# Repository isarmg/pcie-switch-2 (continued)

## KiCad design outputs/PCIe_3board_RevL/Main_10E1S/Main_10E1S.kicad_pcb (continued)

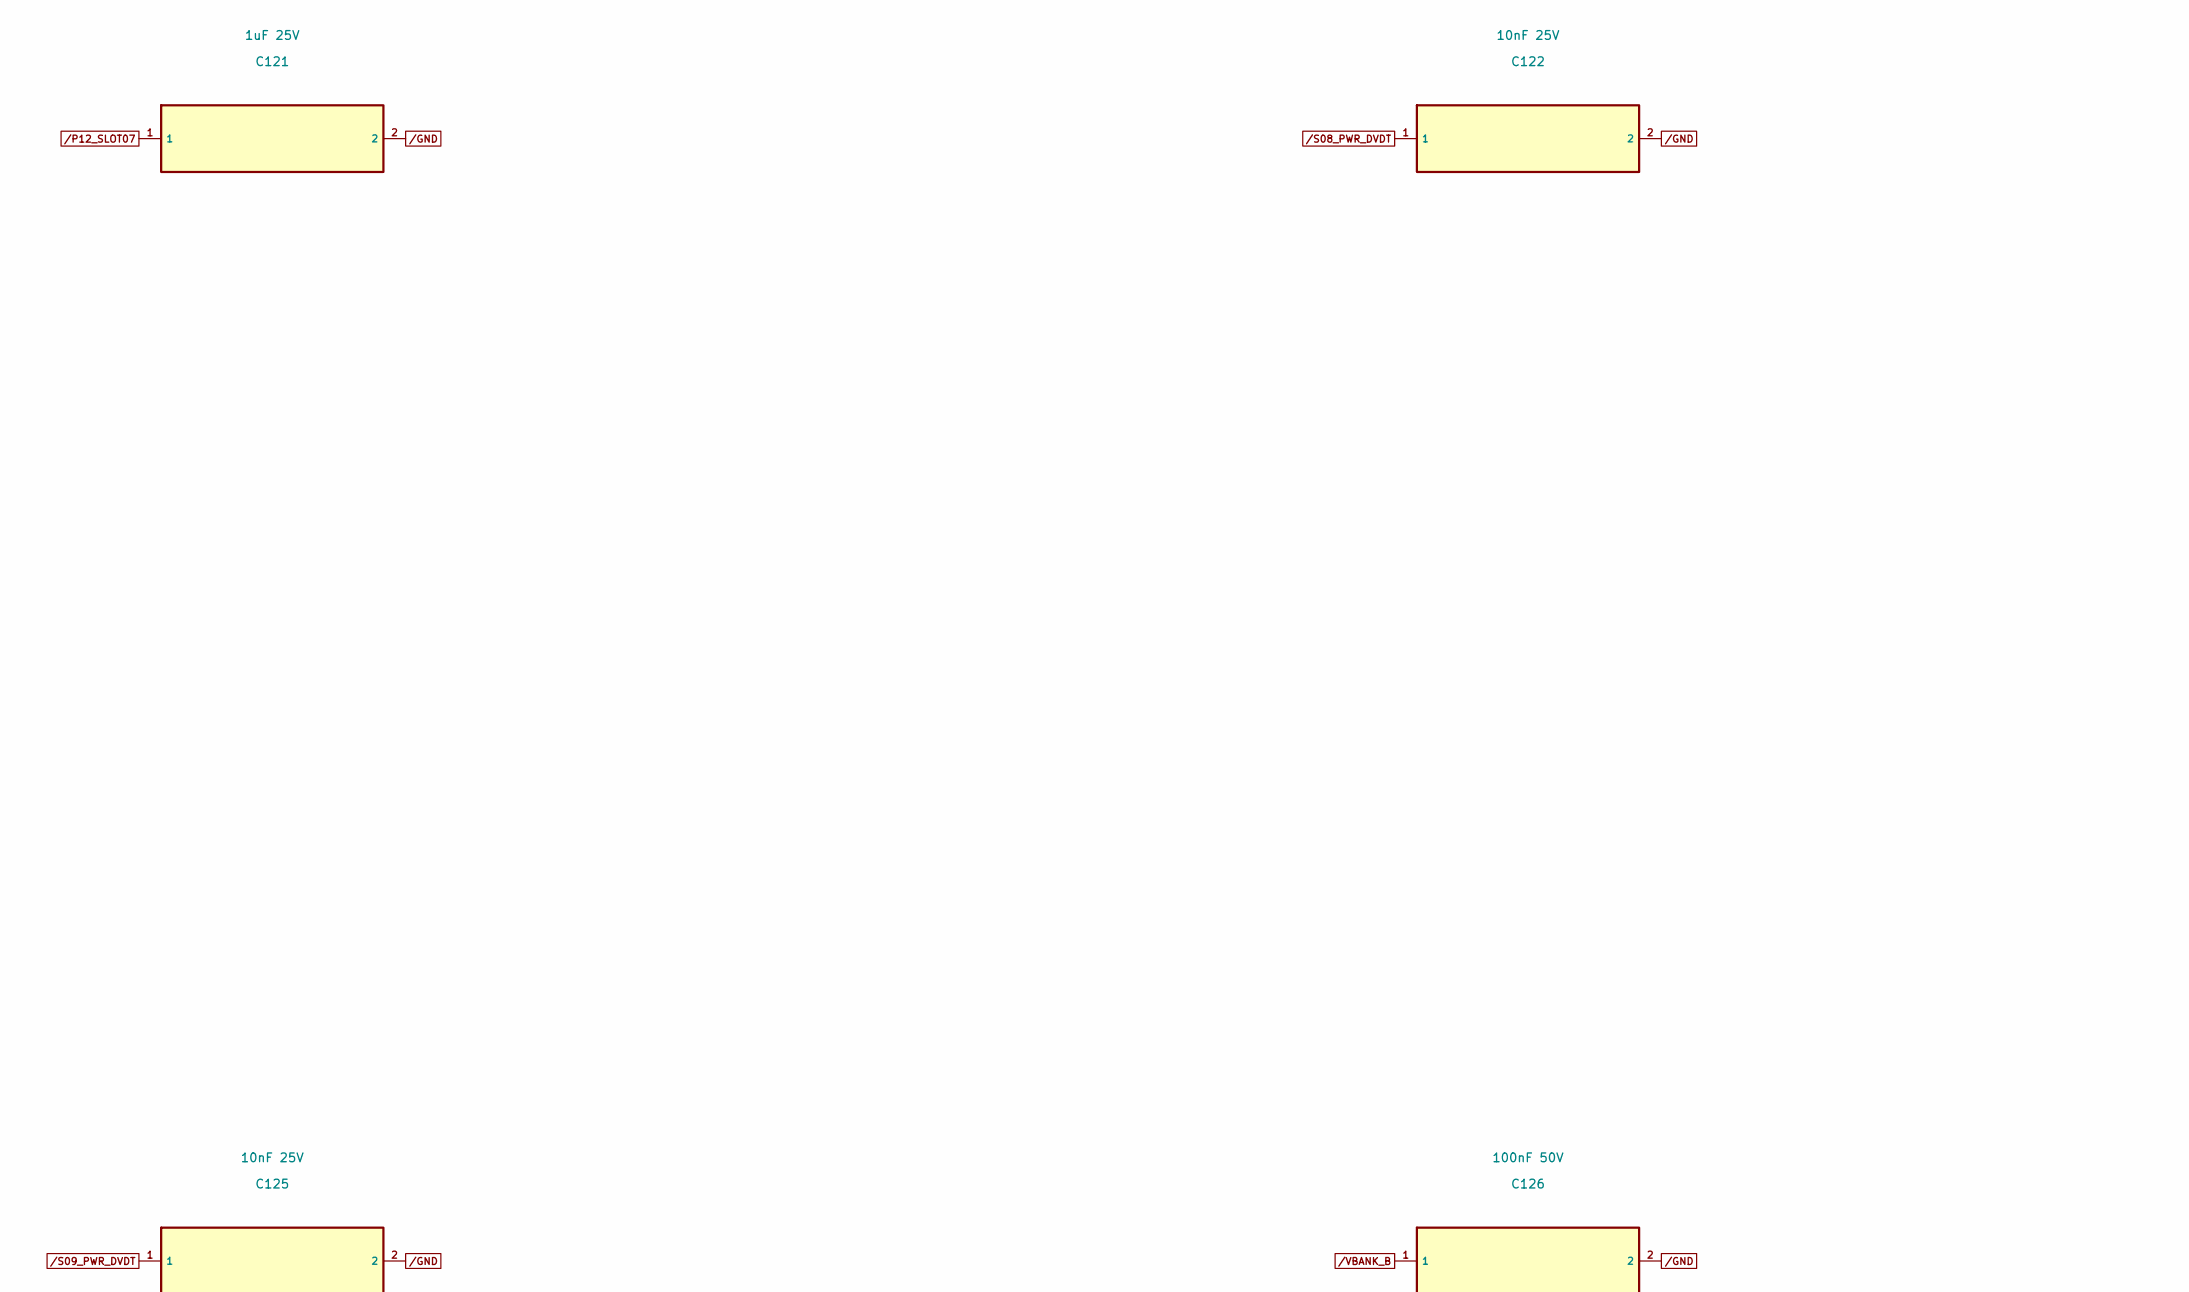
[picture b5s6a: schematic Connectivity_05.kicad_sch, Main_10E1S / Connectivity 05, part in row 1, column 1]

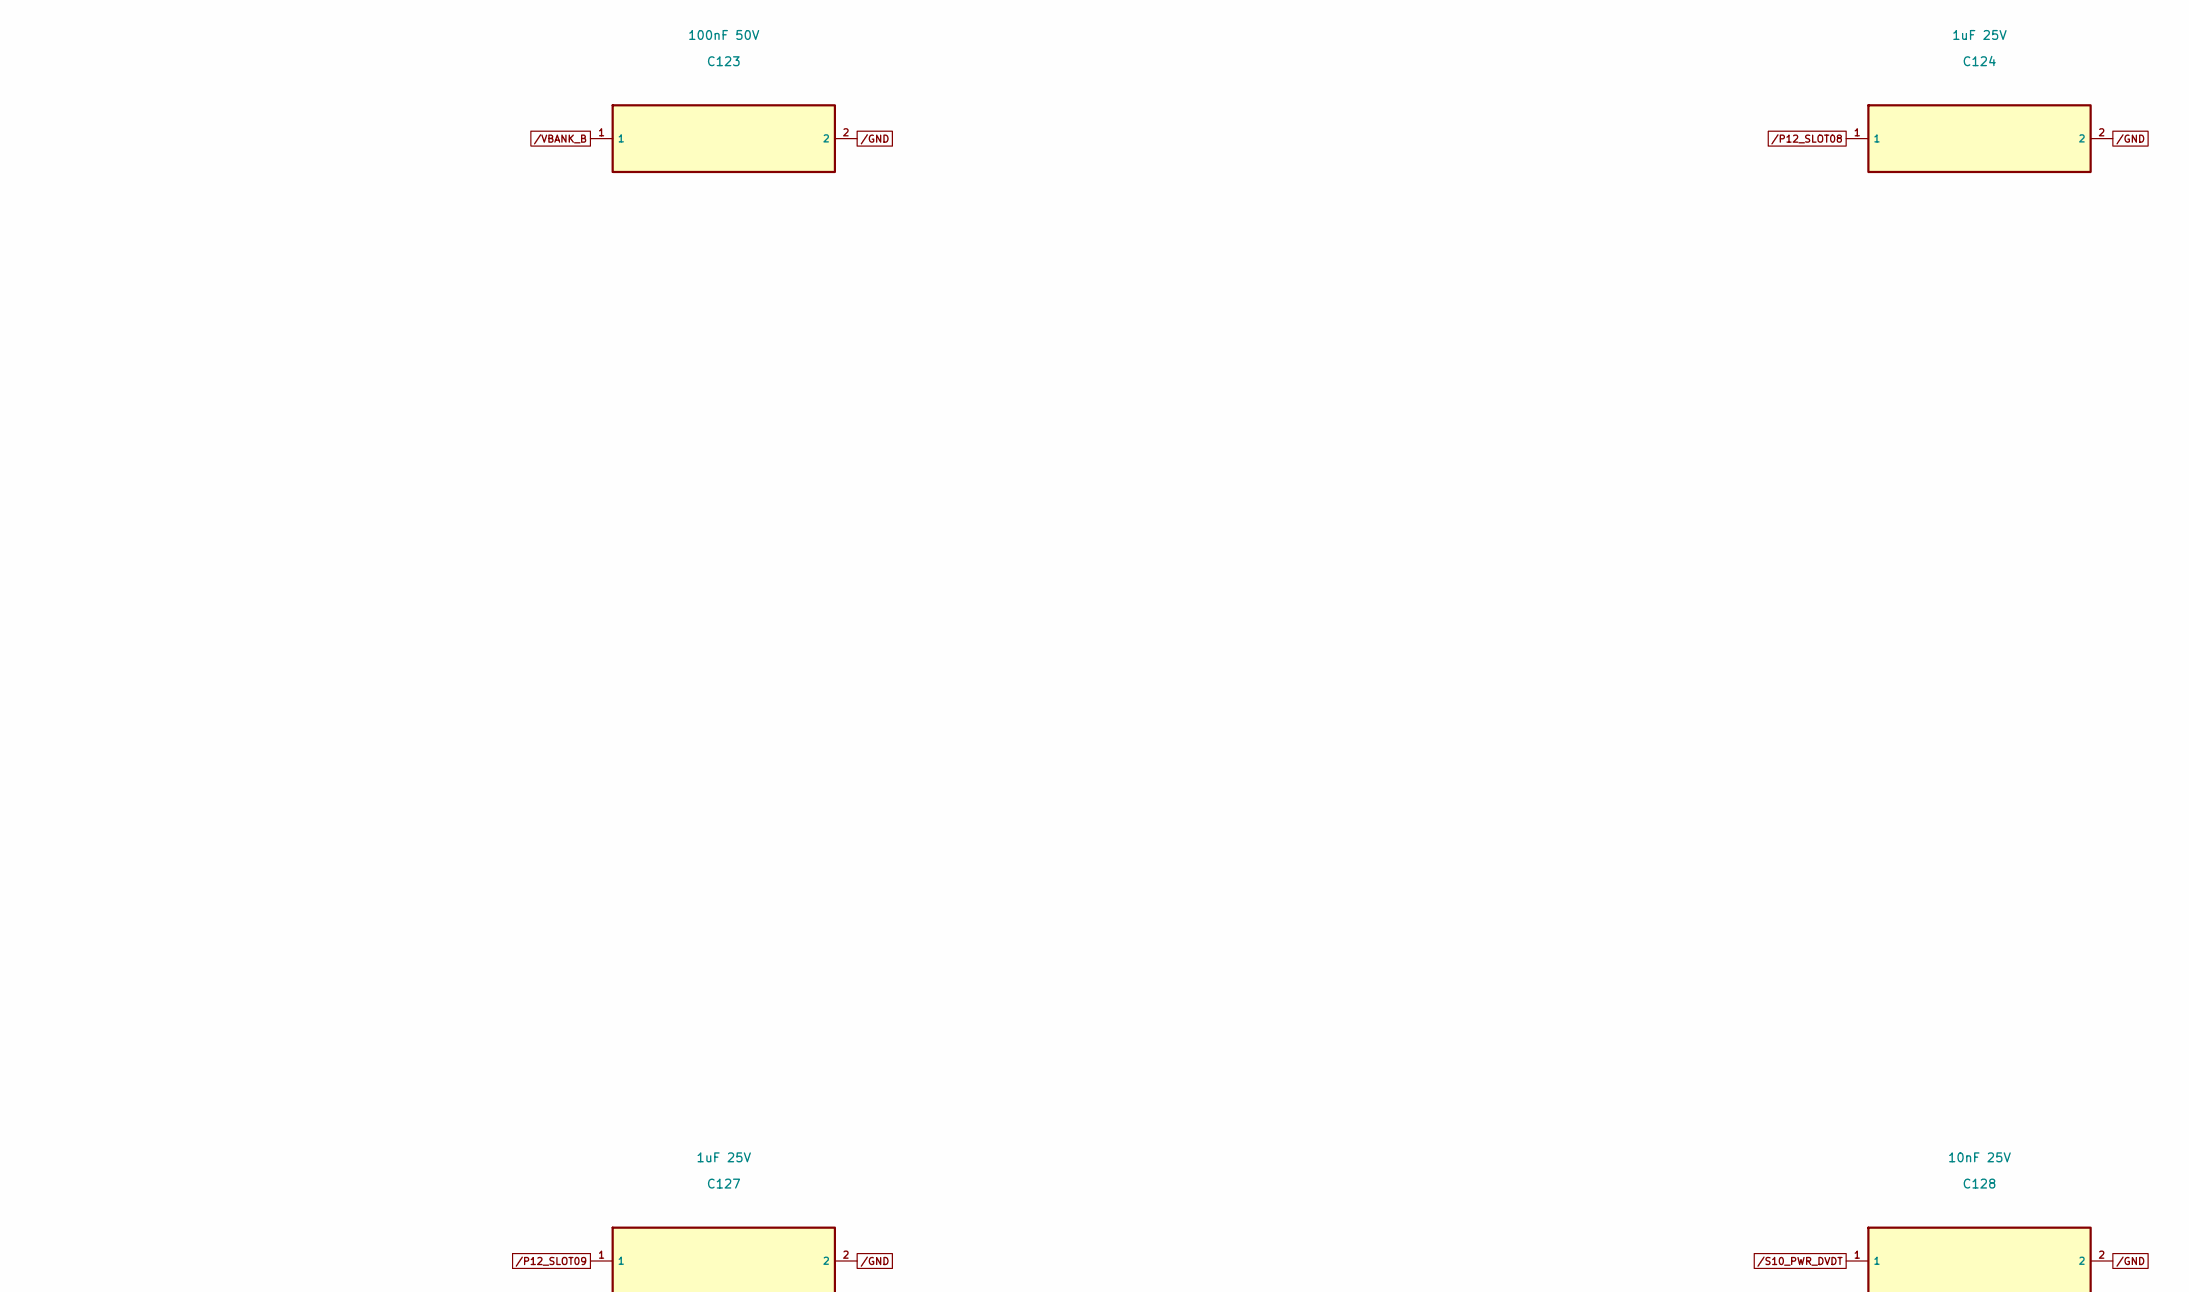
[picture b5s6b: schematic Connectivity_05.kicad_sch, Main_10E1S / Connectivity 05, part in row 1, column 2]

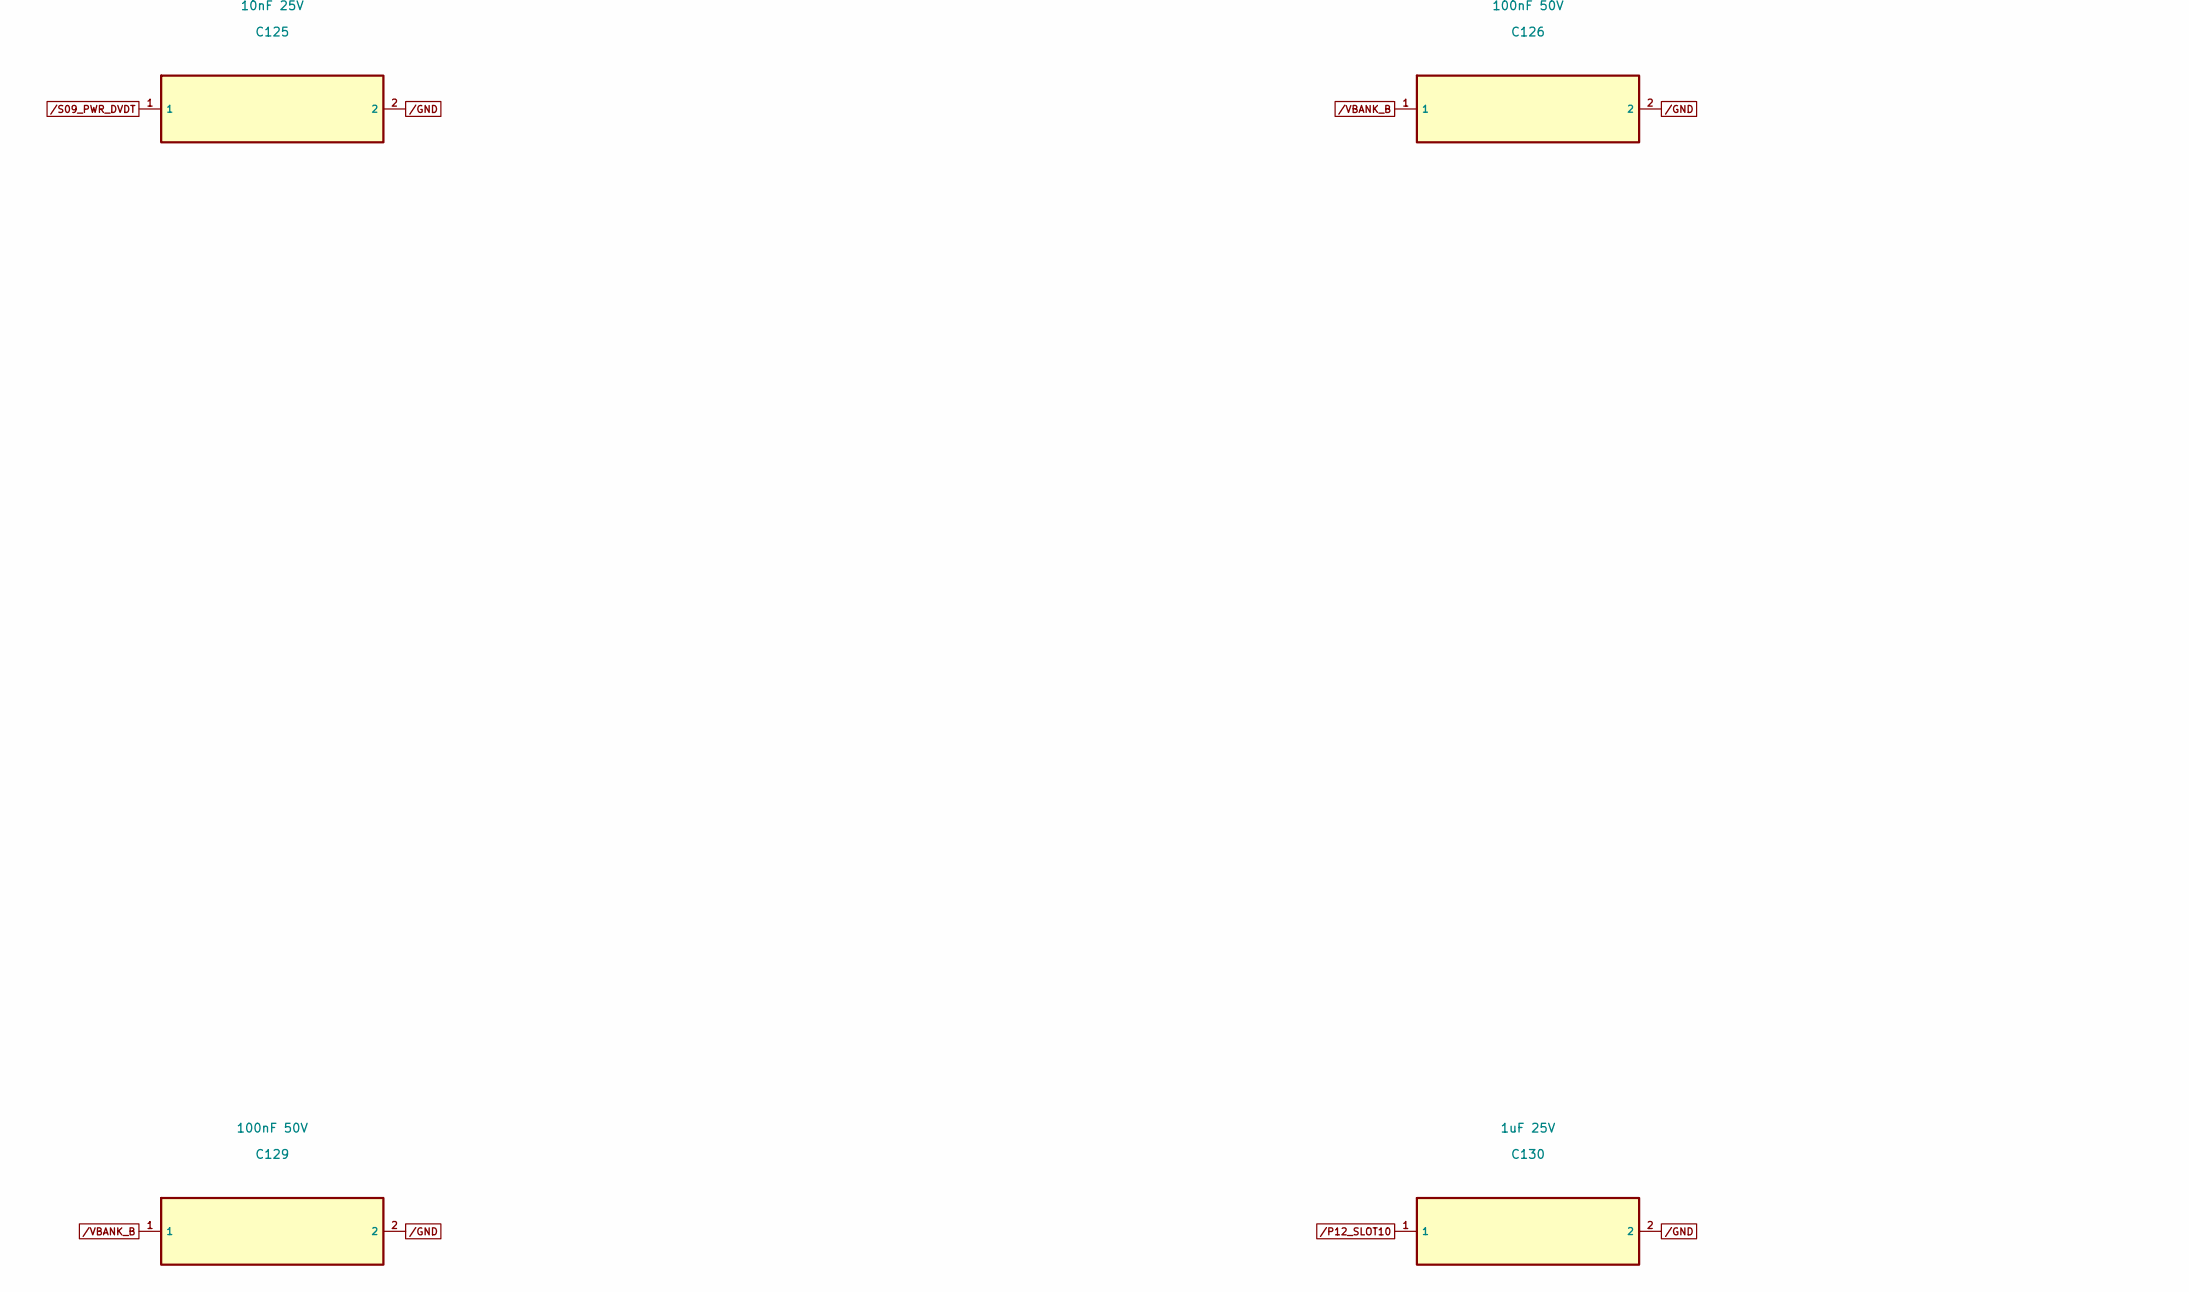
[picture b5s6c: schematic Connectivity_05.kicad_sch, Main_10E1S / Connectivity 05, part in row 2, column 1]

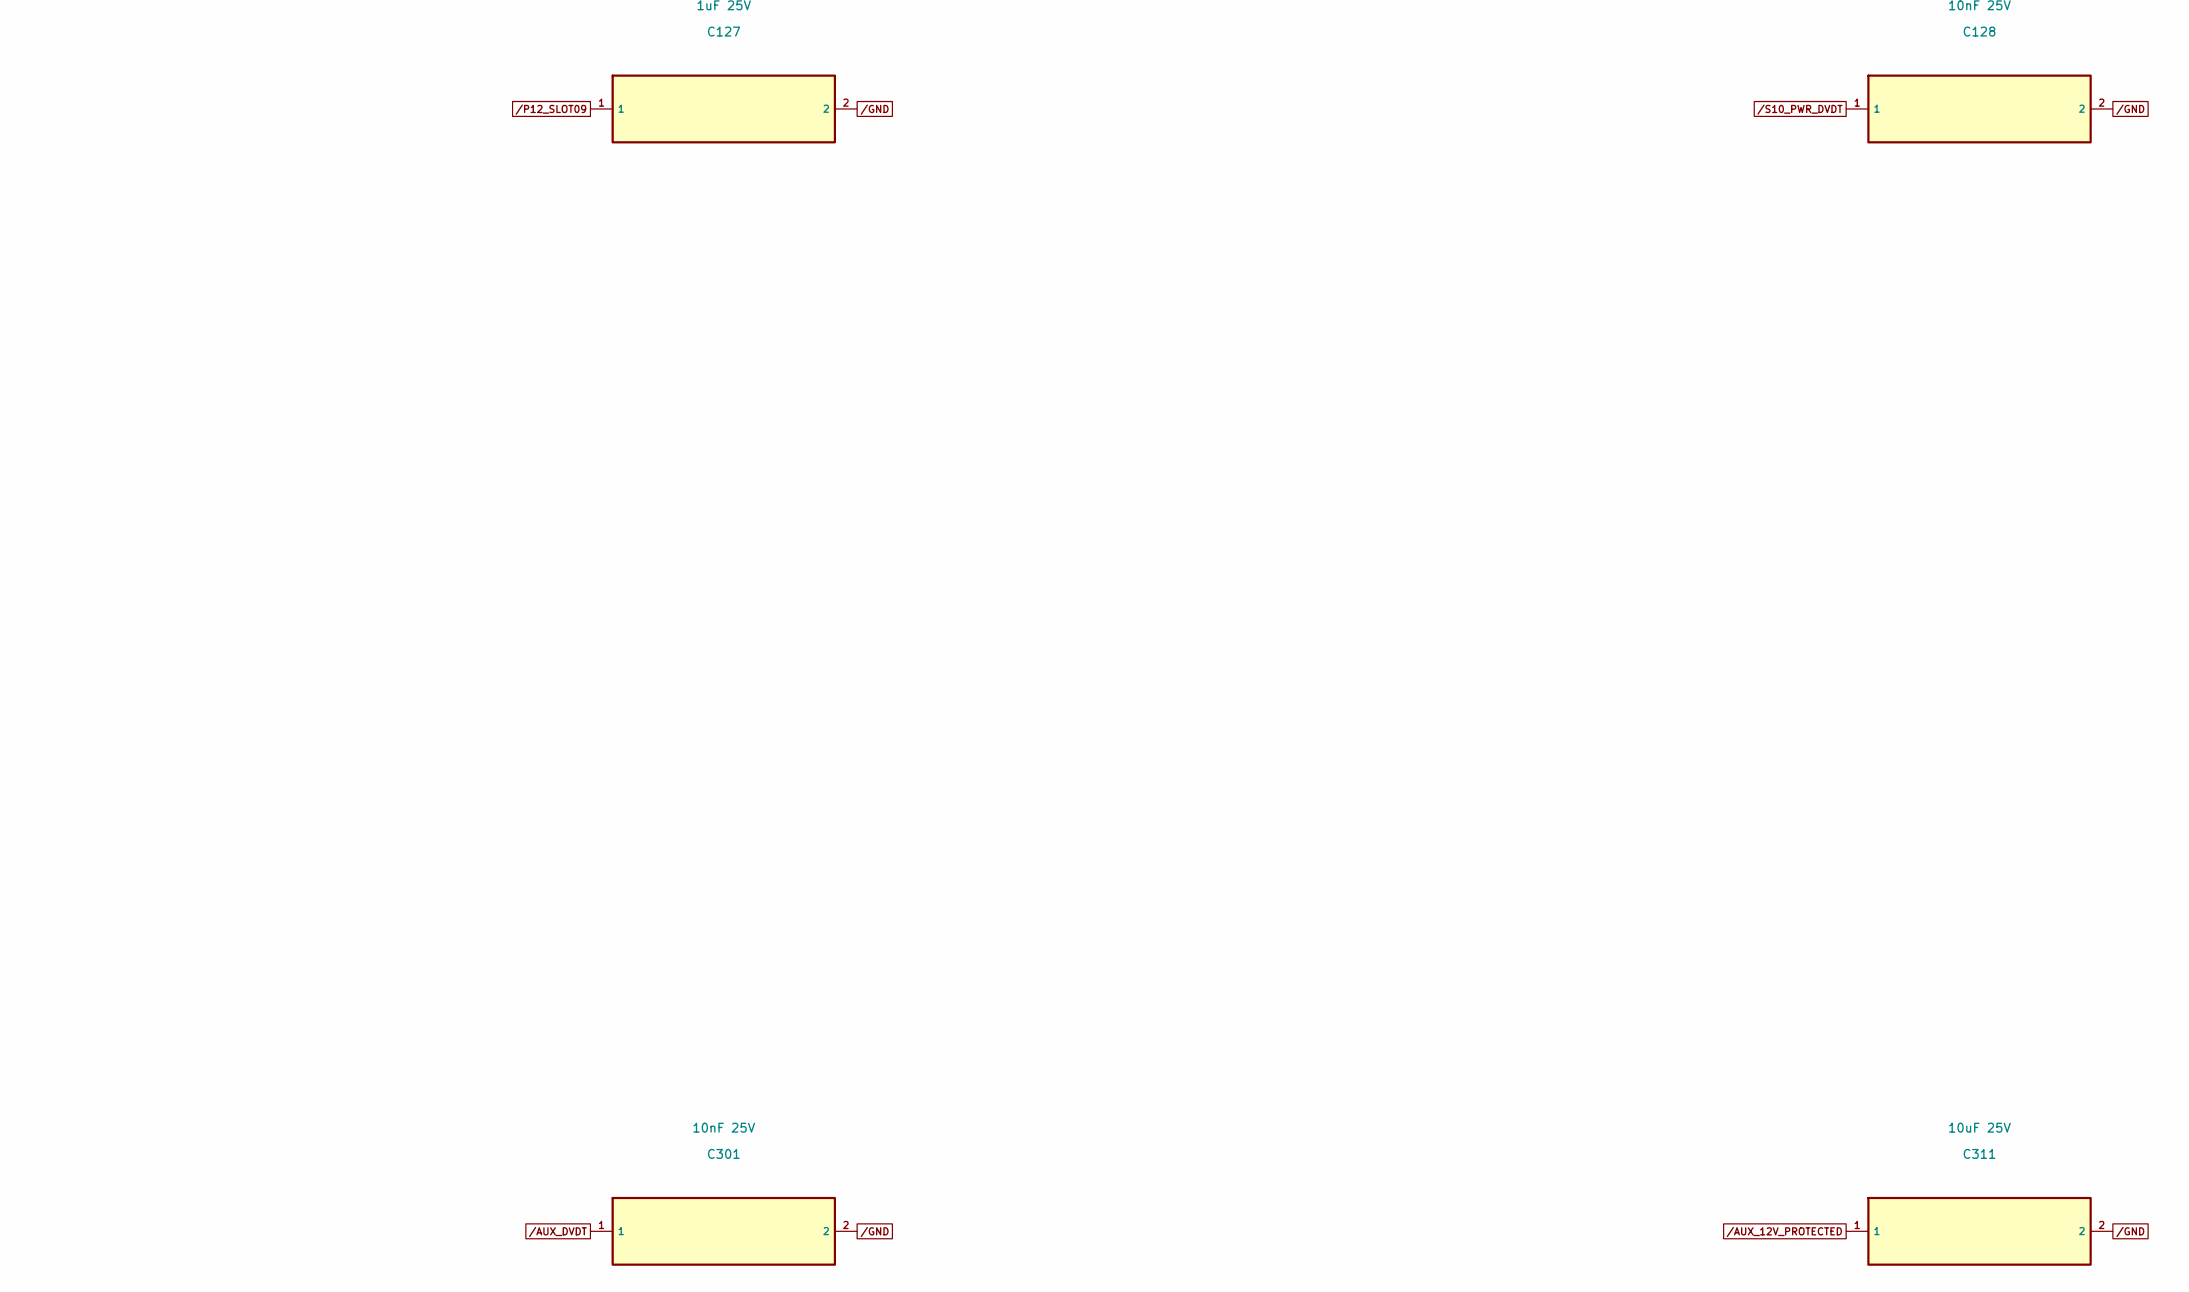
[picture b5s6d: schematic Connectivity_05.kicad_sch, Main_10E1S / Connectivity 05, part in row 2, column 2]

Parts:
C121, C124, C127, C130: 1uF 25V; C_0603_1608Metric
C122, C125, C128, C301: 10nF 25V; C_0402_1005Metric
C123, C126, C129: 100nF 50V; C_0603_1608Metric
C311: 10uF 25V; C_0805_2012Metric

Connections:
/AUX_12V_PROTECTED: C311.1; also elsewhere on the board
/AUX_DVDT: C301.1; also elsewhere on the board
/GND: C121.2, C122.2, C123.2, C124.2, C125.2, C126.2, C127.2, C128.2, C129.2, C130.2, C301.2, C311.2; also elsewhere on the board
/P12_SLOT07: C121.1; also elsewhere on the board
/P12_SLOT08: C124.1; also elsewhere on the board
/P12_SLOT09: C127.1; also elsewhere on the board
/P12_SLOT10: C130.1; also elsewhere on the board
/S08_PWR_DVDT: C122.1; also elsewhere on the board
/S09_PWR_DVDT: C125.1; also elsewhere on the board
/S10_PWR_DVDT: C128.1; also elsewhere on the board
/VBANK_B: C123.1, C126.1, C129.1; also elsewhere on the board
